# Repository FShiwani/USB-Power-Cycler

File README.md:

# USB Power Cycler
A design using an ATMega328P-PU microcontroller to delay the supply of power to an external USB device. It is useful for sensitive USB devices that cannot handle rapid switches in power.

## Purpose
The reason behind the design was to delay the start up of a USB car handsfree receiver that would stop functioning due to power being cycling to the device when switching from the ACC to ON ignition states.

## Design Information
The choice of the microcontroller may seem a slightly too advanced for this project however due to it's popularity and the fact that the Arduino Uno boards use the exact same MCU I chose it to allow a smooth transition between my Arduino prototype over to an independant MCU using the internal 8MHz clock. Depending on how you source your ATMega328P-PU it may come preloaded with a bootloader designed for a 16MHz external crystal such as in the Arduino Uno or it may come with no bootloader burned at all. Either way, you will need to use a different bootloader with the approparite fuses enabled to use the internal clock. More information can be found [here](https://www.arduino.cc/en/Tutorial/ArduinoToBreadboard). An 8-bit DIP switch is used to control the delay time. Values from 0 to 255 seconds are possible with the 8-bits and must be used in binary form. The firmware loaded on the MCU is relatively straight forward and an Arduino sketch is also available. The FDN340P is a logic level p-channel MOSFET is being used as a high side switch for the 5V rail.

## Schematic View

## Board View

## Final Images

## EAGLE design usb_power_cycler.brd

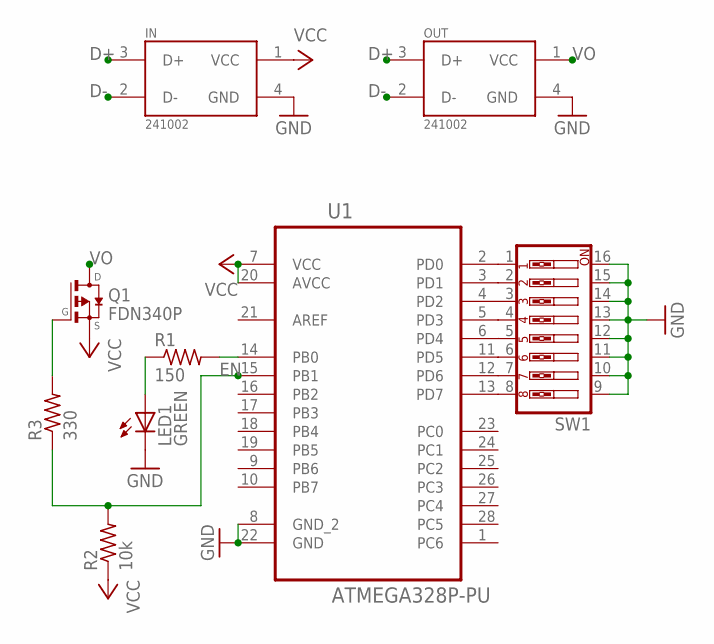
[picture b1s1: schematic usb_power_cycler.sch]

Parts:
IN: 241002; LUMBERG_2410_02
LED1: GREEN; CHIPLED_0805
OUT: 241002; LUMBERG_2410_02
Q1: FDN340P; SSOT-3
R1: 150; R0805
R2: 10k; R0805
R3: 330; R0805
SW1: SW_DIP-8; EDG-08
U1: ATMEGA328P-PU; DIP254P762X457-28

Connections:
D+: IN.3 (D+), OUT.3 (D+)
D-: IN.2 (D-), OUT.2 (D-)
EN: R2.2, R3.1, U1.15 (PB1)
GND: IN.4 (GND), LED1.C, OUT.4 (GND), SW1.9, SW1.10, SW1.11, SW1.12, SW1.13, SW1.14, SW1.15, SW1.16, U1.8 (GND_2), U1.22 (GND)
unnamed: LED1.A, R1.1
unnamed: SW1.1, U1.2 (PD0)
unnamed: SW1.2, U1.3 (PD1)
unnamed: SW1.3, U1.4 (PD2)
unnamed: SW1.4, U1.5 (PD3)
unnamed: SW1.5, U1.6 (PD4)
unnamed: SW1.6, U1.11 (PD5)
unnamed: SW1.7, U1.12 (PD6)
unnamed: SW1.8, U1.13 (PD7)
unnamed: R1.2, U1.14 (PB0)
unnamed: Q1.1 (G), R3.2
VCC: IN.1 (VCC), Q1.2 (S), R2.1, U1.7 (VCC), U1.20 (AVCC)
VO: OUT.1 (VCC), Q1.3 (D)

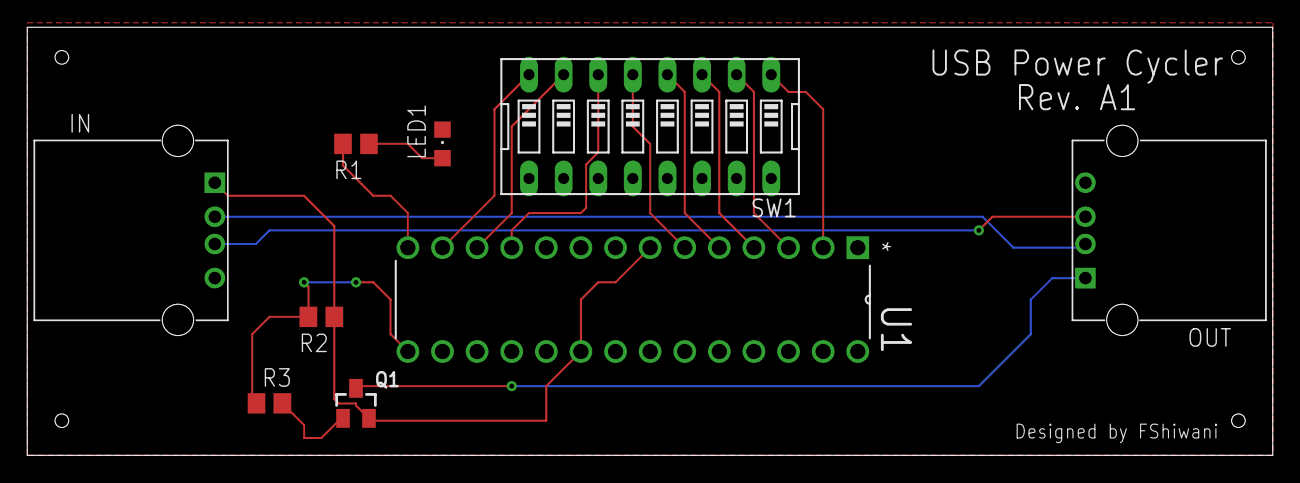
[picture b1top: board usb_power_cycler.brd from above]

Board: 2 copper layers, 91.4 x 31.4 mm, 9 parts (0 on the bottom side), 17 nets.

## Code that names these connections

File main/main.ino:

// ▒█░▒█ ▒█▀▀▀█ ▒█▀▀█ ░░ ▒█▀▀█ ▒█▀▀▀█ ▒█░░▒█ ▒█▀▀▀ ▒█▀▀█ ░░ ▒█▀▀█ ▒█░░▒█ ▒█▀▀█ ▒█░░░ ▒█▀▀▀ ▒█▀▀█ 
// ▒█░▒█ ░▀▀▀▄▄ ▒█▀▀▄ ▀▀ ▒█▄▄█ ▒█░░▒█ ▒█▒█▒█ ▒█▀▀▀ ▒█▄▄▀ ▀▀ ▒█░░░ ▒█▄▄▄█ ▒█░░░ ▒█░░░ ▒█▀▀▀ ▒█▄▄▀ 
// ░▀▄▄▀ ▒█▄▄▄█ ▒█▄▄█ ░░ ▒█░░░ ▒█▄▄▄█ ▒█▄▀▄█ ▒█▄▄▄ ▒█░▒█ ░░ ▒█▄▄█ ░░▒█░░ ▒█▄▄█ ▒█▄▄█ ▒█▄▄▄ ▒█░▒█ 
/* --------------------------------------------------------------------------------------------------------------------------------------------
 *  Project: USB Power Cycler
 *  Author: Fahd Shiwani
 *  Version: Rev. A
 *  Target Microncontroller: ATMega328P-PU
 * --------------------------------------------------------------------------------------------------------------------------------------------
 */

// Pin Declarations
#define ACTIVITY_LED_PIN 8 // PB0
#define ENABLE_PIN 9 // PB1
#define SW_PIN_1 0 // PD0
#define SW_PIN_2 1 // PD1
#define SW_PIN_3 2 // PD2
#define SW_PIN_4 3 // PD3
#define SW_PIN_5 4 // PD4
#define SW_PIN_6 5 // PD5
#define SW_PIN_7 6 // PD6
#define SW_PIN_8 7 // PD7

unsigned int SW_STATE[8]; // DIP switch state

// function to read digital pins for DIP switch.
void readSWState(int SW_STATE[]){
  SW_STATE[0] = !digitalRead(SW_PIN_1); // MSB
  SW_STATE[1] = !digitalRead(SW_PIN_2);
  SW_STATE[2] = !digitalRead(SW_PIN_3);
  SW_STATE[3] = !digitalRead(SW_PIN_4);
  SW_STATE[4] = !digitalRead(SW_PIN_5);
  SW_STATE[5] = !digitalRead(SW_PIN_6);
  SW_STATE[6] = !digitalRead(SW_PIN_7);
  SW_STATE[7] = !digitalRead(SW_PIN_8); // LSB
}

// function to convert from binary switch state values to integer delay.
int convertSW(int SW_STATE[]){
  unsigned int delay = 0;
  
  for(int i=0; i<8; i++){
    delay = (delay << 1) + SW_STATE[i];
  }
  Serial.print("Requested Delay: ");
  Serial.print(delay);
  Serial.print(" seconds");
  return delay;
}

void setup() {
  Serial.begin(9600);
  
  // Intializing Pins
  pinMode(ACTIVITY_LED_PIN, OUTPUT);
  pinMode(ENABLE_PIN, OUTPUT);
  pinMode(SW_PIN_1, INPUT_PULLUP); // enabling internal pull-ups.
  pinMode(SW_PIN_2, INPUT_PULLUP);
  pinMode(SW_PIN_3, INPUT_PULLUP);
  pinMode(SW_PIN_4, INPUT_PULLUP);
  pinMode(SW_PIN_5, INPUT_PULLUP);
  pinMode(SW_PIN_6, INPUT_PULLUP);
  pinMode(SW_PIN_7, INPUT_PULLUP);
  pinMode(SW_PIN_8, INPUT_PULLUP);

  readSWState(SW_STATE);
  digitalWrite(ACTIVITY_LED_PIN, HIGH);
  digitalWrite(ENABLE_PIN, HIGH); // active-low enable.
  delay(convertSW(SW_STATE)*1000L); // converted to milliseconds
  digitalWrite(ENABLE_PIN, LOW); 
  digitalWrite(ACTIVITY_LED_PIN, LOW);
}

void loop() {

}

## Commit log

2018-01-20 Add sketch and board/schematic files
